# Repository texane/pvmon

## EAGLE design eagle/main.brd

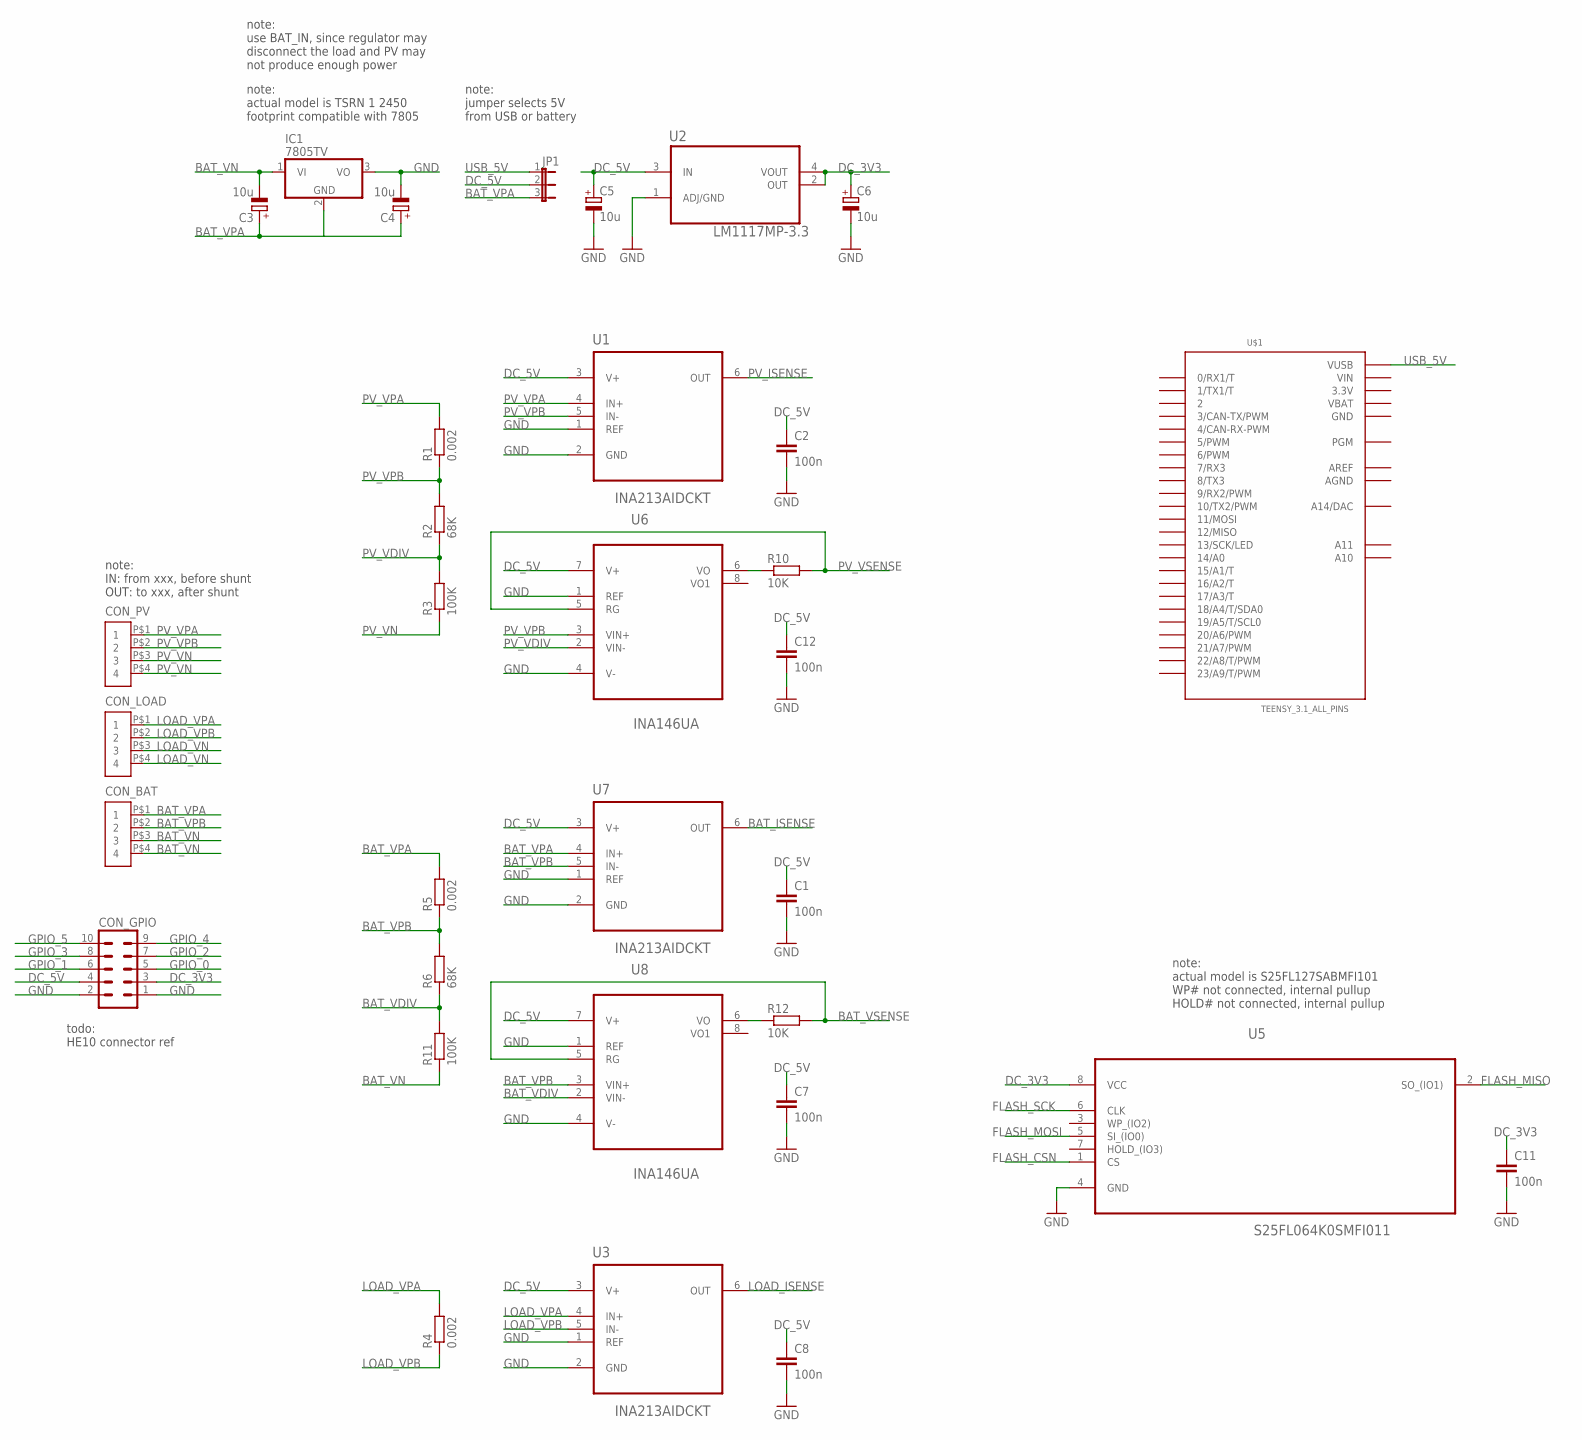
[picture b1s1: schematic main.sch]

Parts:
C1, C2, C7, C8, C11, C12: 100n; C1206
C3, C4, C5, C6: 10u; CT3528
CON_BAT: MC000036
CON_GPIO: MA05-2
CON_LOAD: MC000036
CON_PV: MC000036
IC1: 7805TV; TO220V
JP1: JP2E; JP2
R1, R4, R5: 0.002; R2512
R2, R6: 68K; R0603
R3, R11: 100K; R0603
R10, R12: 10K; R0603
U1, U3, U7: INA213AIDCKT; SOT65P210X110-6N
U2: LM1117MP-3.3; SOT230P696X180-4N
U5: S25FL064K0SMFI011; SOIC127P800X215-8N
U6, U8: INA146UA; SOIC127P600X175-8N
U$1: TEENSY_3.1_ALL_PINS; TEENSY3-ALL_PINS

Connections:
3.3V: U$1.3.3V, U$1.3.3V1 (3.3V)
AGND: U$1.AGND
AREF: U$1.AREF
BAT_ISENSE: U7.6 (OUT)
BAT_VDIV: R6.1, R11.2, U8.2 (VIN-)
BAT_VN: C3.-, CON_BAT.P$3 (3), CON_BAT.P$4 (4), IC1.1 (VI), R11.1
BAT_VPA: C3.+, C4.+, CON_BAT.P$1 (1), JP1.3, R5.2, U7.4 (IN+)
BAT_VPB: CON_BAT.P$2 (2), R5.1, R6.2, U7.5 (IN-), U8.3 (VIN+)
BAT_VSENSE: R12.2, U8.5 (RG)
DC_3V3: C6.+, C11.1, CON_GPIO.3, U2.2 (OUT), U2.4 (VOUT), U5.8 (VCC)
DC_5V: C1.1, C2.1, C5.+, C7.1, C8.1, C12.1, CON_GPIO.4, JP1.2, U1.3 (V+), U2.3 (IN), U3.3 (V+), U6.7 (V+), U7.3 (V+), U8.7 (V+)
FLASH_CSN: U5.1 (CS)
FLASH_MISO: U5.2 (SO_(IO1))
FLASH_MOSI: U5.5 (SI_(IO0))
FLASH_SCK: U5.6 (CLK)
GND: C1.2, C2.2, C4.-, C5.-, C6.-, C7.2, C8.2, C11.2, C12.2, CON_GPIO.1, CON_GPIO.2, IC1.3 (VO), U1.1 (REF), U1.2 (GND), U2.1 (ADJ/GND), U3.1 (REF), U3.2 (GND), U5.4 (GND), U6.1 (REF), U6.4 (V-), U7.1 (REF), U7.2 (GND), U8.1 (REF), U8.4 (V-), U$1.GND, U$1.GND1 (GND)
GPIO_0: CON_GPIO.5
GPIO_1: CON_GPIO.6
GPIO_2: CON_GPIO.7
GPIO_3: CON_GPIO.8
GPIO_4: CON_GPIO.9
GPIO_5: CON_GPIO.10
LOAD_ISENSE: U3.6 (OUT)
LOAD_VN: CON_LOAD.P$3 (3), CON_LOAD.P$4 (4)
LOAD_VPA: CON_LOAD.P$1 (1), R4.2, U3.4 (IN+)
LOAD_VPB: CON_LOAD.P$2 (2), R4.1, U3.5 (IN-)
unnamed: R12.1, U8.6 (VO)
unnamed: R10.1, U6.6 (VO)
PV_ISENSE: U1.6 (OUT)
PV_VDIV: R2.1, R3.2, U6.2 (VIN-)
PV_VN: CON_PV.P$3 (3), CON_PV.P$4 (4), R3.1
PV_VPA: CON_PV.P$1 (1), R1.2, U1.4 (IN+)
PV_VPB: CON_PV.P$2 (2), R1.1, R2.2, U1.5 (IN-), U6.3 (VIN+)
PV_VSENSE: R10.2, U6.5 (RG)
USB_5V: JP1.1, U$1.VUSB
VBAT: U$1.VBAT
VIN: U$1.VIN

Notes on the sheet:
note: actual model is TSRN 1 2450 footprint compatible with 7805
note: jumper selects 5V from USB or battery
note: IN: from xxx, before shunt OUT: to xxx, after shunt
todo: HE10 connector ref
note: use BAT_IN, since regulator may disconnect the load and PV may not produce enough power
note: actual model is S25FL127SABMFI101 WP# not connected, internal pullup HOLD# not connected, internal pullup

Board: 2 copper layers, 33 parts (0 on the bottom side), 20 nets, no tracks yet.

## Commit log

2016-06-07 add doc/notes
2016-06-07 add eagle
2016-06-07 add eagle/main.brd, eagle/lib/misc
2016-06-08 add microsd
2016-06-09 add Spansion flash memory
2016-06-12 add dia
2016-06-12 scale doc/dia/overview/main.png
2016-06-12 clarify doc/dia/monitor
2016-06-12 doc/dia/monitor, voltage measure stage
2016-06-13 add TI library
2016-06-13 rename dia/overview to dia/wiring
2016-06-13 rename PV, BAT, LOAD signals
2016-06-13 doc/dia/wiring, swap LOAD_VPA
